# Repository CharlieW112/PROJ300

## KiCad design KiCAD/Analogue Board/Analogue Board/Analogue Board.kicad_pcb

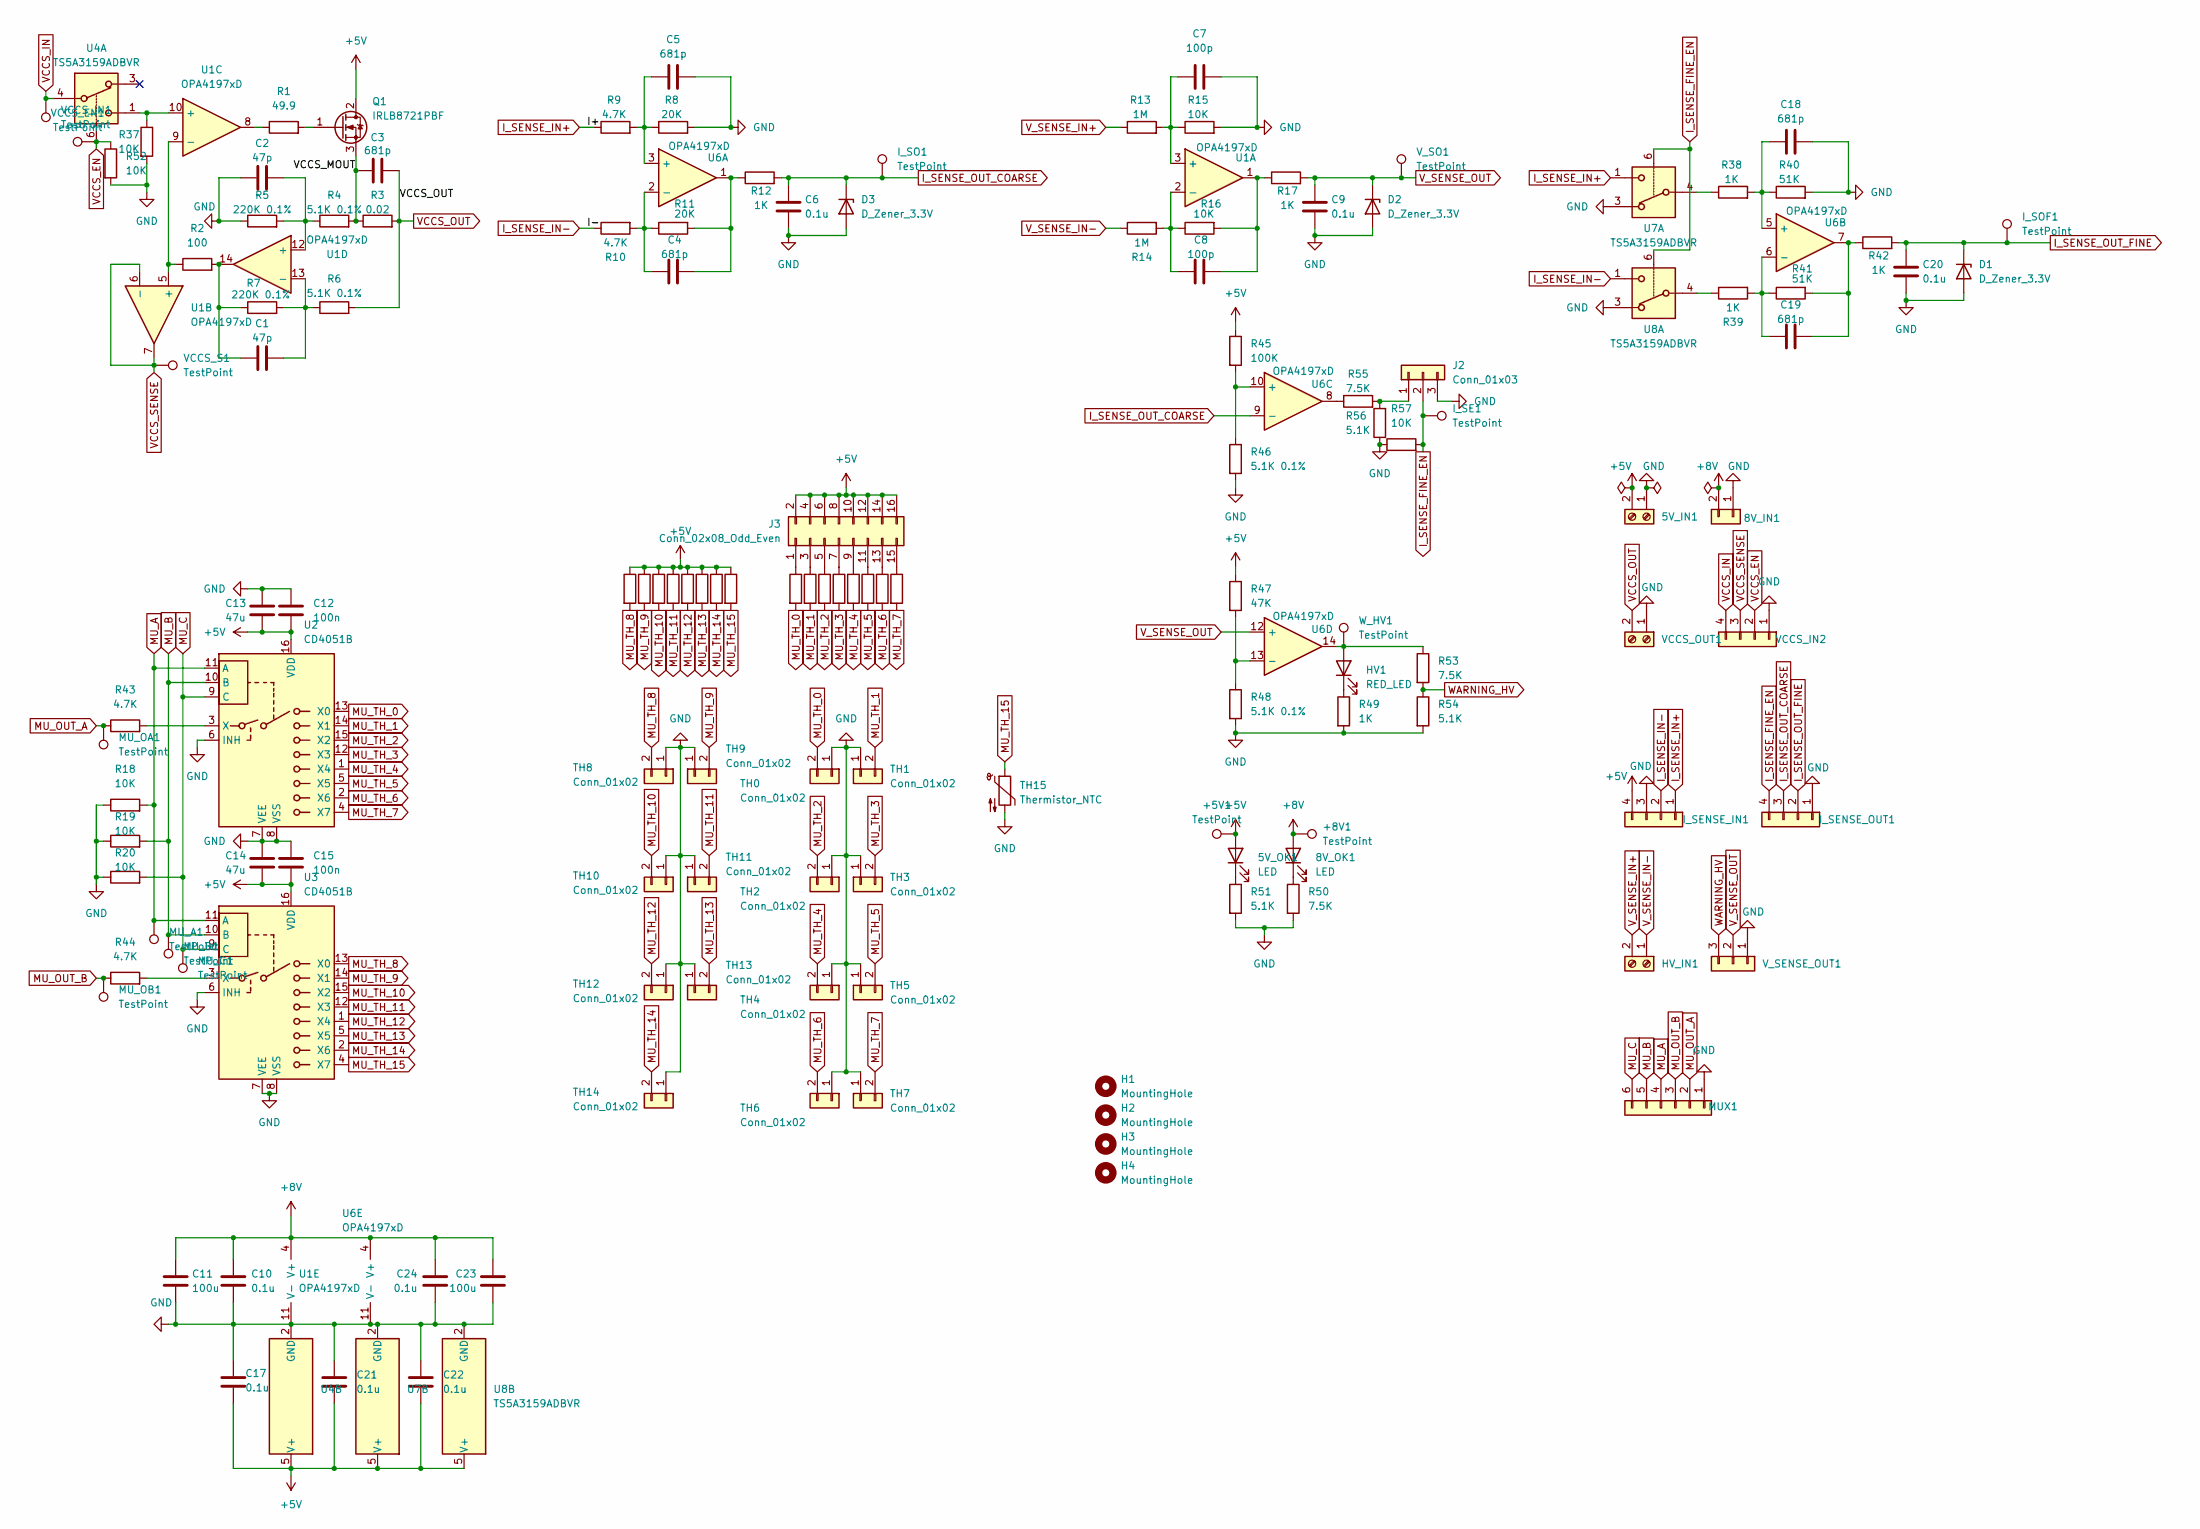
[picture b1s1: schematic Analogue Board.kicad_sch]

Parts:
5V_IN1: Screw_Terminal_01x02; TerminalBlock_bornier-2_P5.08mm
5V_OK1, 8V_OK1: LED; D_0603_1608Metric_Pad1.05x0.95mm_HandSolder
8V_IN1: Conn_01x02; JST_XH_B2B-XH-A_1x02_P2.50mm_Vertical
+5V1, +8V1: TestPoint; TestPoint_Pad_1.5x1.5mm
C1, C2: 47p; C_0201_0603Metric_Pad0.64x0.40mm_HandSolder
C3, C4, C5, C18, C19: 681p; C_0201_0603Metric_Pad0.64x0.40mm_HandSolder
C6, C9, C10, C17, C20, C21, C22, C24: 0.1u; C_0603_1608Metric_Pad1.08x0.95mm_HandSolder
C7, C8: 100p; C_0402_1005Metric_Pad0.74x0.62mm_HandSolder
C11, C23: 100u; C_Radial_D6.3mm_H11.0mm_P2.50mm
C12, C15: 100n; C_0603_1608Metric_Pad1.08x0.95mm_HandSolder
C13, C14: 47u; C_Radial_D6.3mm_H11.0mm_P2.50mm
D1, D2, D3: D_Zener_3.3V; D_SOD-123
H1, H2, H3, H4: MountingHole; MountingHole_3.2mm_M3
HV1: RED_LED; D_0603_1608Metric_Pad1.05x0.95mm_HandSolder
HV_IN1: Screw_Terminal_01x02; TerminalBlock_bornier-2_P5.08mm
I_SE1: TestPoint; TestPoint_Pad_1.5x1.5mm
I_SENSE_IN1: Conn_01x04; JST_XH_B4B-XH-A_1x04_P2.50mm_Vertical
I_SENSE_OUT1: Conn_01x04; JST_XH_B4B-XH-A_1x04_P2.50mm_Vertical
I_SO1: TestPoint; TestPoint_Pad_1.5x1.5mm
I_SOF1: TestPoint; TestPoint_Pad_1.5x1.5mm
J2: Conn_01x03; PinHeader_1x03_P2.54mm_Vertical
J3: Conn_02x08_Odd_Even; PinHeader_2x08_P2.54mm_Vertical
MUX1: Conn_01x06; JST_XH_B6B-XH-A_1x06_P2.50mm_Vertical
MU_A1: TestPoint; TestPoint_Pad_1.5x1.5mm
MU_B1: TestPoint; TestPoint_Pad_1.5x1.5mm
MU_C1: TestPoint; TestPoint_Pad_1.5x1.5mm
MU_OA1: TestPoint; TestPoint_Pad_1.5x1.5mm
MU_OB1: TestPoint; TestPoint_Pad_1.5x1.5mm
Q1: IRLB8721PBF; TO-220-3_Vertical
R1: 49.9; R_0402_1005Metric_Pad0.72x0.64mm_HandSolder
R2: 100; R_0603_1608Metric_Pad0.98x0.95mm_HandSolder
R3: 0.02; R_2010_5025Metric_Pad1.40x2.65mm_HandSolder
R4, R6, R46, R48: 5.1K 0.1%; R_0603_1608Metric_Pad0.98x0.95mm_HandSolder
R5, R7: 220K 0.1%; R_0805_2012Metric_Pad1.20x1.40mm_HandSolder
R8, R11: 20K; R_0402_1005Metric_Pad0.72x0.64mm_HandSolder
R9, R10, R43, R44: 4.7K; R_0603_1608Metric_Pad0.98x0.95mm_HandSolder
R12, R17, R38, R39, R42, R49: 1K; R_0603_1608Metric_Pad0.98x0.95mm_HandSolder
R13, R14: 1M; R_Axial_DIN0207_L6.3mm_D2.5mm_P7.62mm_Horizontal
R15, R16, R18, R19, R20, R37, R52, R57: 10K; R_0603_1608Metric_Pad0.98x0.95mm_HandSolder
R21, R22, R23, R24, R25, R26, R27, R28, R29, R30, R31, R32, R33, R34, R35, R36: 10K 0.5%; R_0805_2012Metric_Pad1.20x1.40mm_HandSolder
R40, R41: 51K; R_0603_1608Metric_Pad0.98x0.95mm_HandSolder
R45: 100K; R_0402_1005Metric_Pad0.72x0.64mm_HandSolder
R47: 47K; R_0603_1608Metric_Pad0.98x0.95mm_HandSolder
R50, R53, R55: 7.5K; R_0603_1608Metric_Pad0.98x0.95mm_HandSolder
R51, R54, R56: 5.1K; R_0603_1608Metric_Pad0.98x0.95mm_HandSolder
TH0, TH1, TH2, TH3, TH4, TH5, TH6, TH7, TH8, TH9, TH10, TH11, TH12, TH13, TH14: Conn_01x02; JST_XH_B2B-XH-A_1x02_P2.50mm_Vertical
TH15: Thermistor_NTC; R_0805_2012Metric_Pad1.20x1.40mm_HandSolder
U1, U6: OPA4197xD; SOIC-14_3.9x8.7mm_P1.27mm
U2, U3: CD4051B; DIP-16_W7.62mm
U4, U7, U8: TS5A3159ADBVR; SOT-23-6
VCCS_EN1: TestPoint; TestPoint_Pad_1.5x1.5mm
VCCS_IN1: TestPoint; TestPoint_Pad_1.5x1.5mm
VCCS_IN2: Conn_01x04; JST_XH_B4B-XH-A_1x04_P2.50mm_Vertical
VCCS_OUT1: Screw_Terminal_01x02; TerminalBlock_bornier-2_P5.08mm
VCCS_S1: TestPoint; TestPoint_Pad_1.5x1.5mm
V_SENSE_OUT1: Conn_01x03; JST_XH_B3B-XH-A_1x03_P2.50mm_Vertical
V_SO1: TestPoint; TestPoint_Pad_1.5x1.5mm
W_HV1: TestPoint; TestPoint_Pad_1.5x1.5mm

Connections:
+5V: 5V_IN1.2, 5V_OK1.2 (A), +5V1.1, C12.2, C13.2, C14.2, C15.2, C17.2, C21.2, C22.2, I_SENSE_IN1.4, J3.2, J3.4, J3.6, J3.8, J3.10, J3.12, J3.14, J3.16, Q1.2 (D), R29.1, R30.1, R31.1, R32.1, R33.1, R34.1, R35.1, R36.1, R45.1, R47.1, U2.16 (VDD), U3.16 (VDD), U4.5 (V+), U7.5 (V+), U8.5 (V+)
+8V: 8V_IN1.2, 8V_OK1.2 (A), +8V1.1, C10.1, C11.1, C23.1, C24.1, U1.4 (V+), U6.4 (V+)
/VCCS_MOUT: C3.1, Q1.3 (S), R3.1, R4.2
GND: 5V_IN1.1, 8V_IN1.1, C2.1, C5.2, C6.2, C7.2, C9.2, C10.2, C11.2, C12.1, C13.1, C14.1, C15.1, C17.1, C18.2, C20.2, C21.1, C22.1, C23.2, C24.2, D1.2 (A), D2.2 (A), D3.2 (A), I_SENSE_IN1.3, I_SENSE_OUT1.1, J2.3, MUX1.1, R5.1, R8.2, R15.2, R18.1, R19.1, R20.1, R37.2, R40.2, R46.2, R48.2, R49.2, R50.2, R51.2, R52.2, R54.2, R56.1, R57.1, TH0.1, TH1.1, TH2.1, TH3.1, TH4.1, TH5.1, TH6.1, TH7.1, TH8.1, TH9.1, TH10.1, TH11.1, TH12.1, TH13.1, TH14.1, TH15.2, U1.11 (V-), U2.6 (INH), U2.7 (VEE), U2.8 (VSS), U3.6 (INH), U3.7 (VEE), U3.8 (VSS), U4.2 (GND), U6.11 (V-), U7.2 (GND), U7.3, U8.2 (GND), U8.3, VCCS_IN2.1, VCCS_OUT1.1, V_SENSE_OUT1.1
I_SENSE_FINE_EN: I_SE1.1, I_SENSE_OUT1.4, J2.2, R57.2, U7.6, U8.6
I_SENSE_IN+: I_SENSE_IN1.1, R9.1, U7.1
I_SENSE_IN-: I_SENSE_IN1.2, R10.1, U8.1
I_SENSE_OUT_COARSE: C6.1, D3.1 (K), I_SENSE_OUT1.3, I_SO1.1, R12.2, U6.9 (-)
I_SENSE_OUT_FINE: C20.1, D1.1 (K), I_SENSE_OUT1.2, I_SOF1.1, R42.2
MU_A: MUX1.4, MU_A1.1, R18.2, U2.11 (A), U3.11 (A)
MU_B: MUX1.5, MU_B1.1, R19.2, U2.10 (B), U3.10 (B)
MU_C: MUX1.6, MU_C1.1, R20.2, U2.9 (C), U3.9 (C)
MU_OUT_A: MUX1.2, MU_OA1.1, R43.1
MU_OUT_B: MUX1.3, MU_OB1.1, R44.1
MU_TH_0: R21.2, TH0.2, U2.13 (X0)
MU_TH_1: R22.2, TH1.2, U2.14 (X1)
MU_TH_2: R23.2, TH2.2, U2.15 (X2)
MU_TH_3: R24.2, TH3.2, U2.12 (X3)
MU_TH_4: R25.2, TH4.2, U2.1 (X4)
MU_TH_5: R26.2, TH5.2, U2.5 (X5)
MU_TH_6: R27.2, TH6.2, U2.2 (X6)
MU_TH_7: R28.2, TH7.2, U2.4 (X7)
MU_TH_8: R29.2, TH8.2, U3.13 (X0)
MU_TH_9: R30.2, TH9.2, U3.14 (X1)
MU_TH_10: R31.2, TH10.2, U3.15 (X2)
MU_TH_11: R32.2, TH11.2, U3.12 (X3)
MU_TH_12: R33.2, TH12.2, U3.1 (X4)
MU_TH_13: R34.2, TH13.2, U3.5 (X5)
MU_TH_14: R35.2, TH14.2, U3.2 (X6)
MU_TH_15: R36.2, TH15.1, U3.4 (X7)
unnamed: 5V_OK1.1 (K), R51.1
unnamed: 8V_OK1.1 (K), R50.1
unnamed: C1.1, R2.2, R7.1, U1.14
unnamed: C4.2, R11.2, R12.1, U6.1
unnamed: C8.2, R16.2, R17.1, U1.1
unnamed: C19.2, R41.2, R42.1, U6.7
unnamed: HV1.2 (A), R53.1, U6.14, W_HV1.1
unnamed: HV1.1 (K), R49.1
unnamed: J2.1, R55.2, R56.2
unnamed: J3.1, R21.1
unnamed: J3.3, R22.1
unnamed: J3.5, R23.1
unnamed: J3.7, R24.1
unnamed: J3.9, R25.1
unnamed: J3.11, R26.1
unnamed: J3.13, R27.1
unnamed: J3.15, R28.1
unnamed: Q1.1 (G), R1.2
unnamed: R1.1, U1.8
unnamed: R38.1, U7.4
unnamed: R39.1, U8.4
unnamed: R55.1, U6.8
unnamed: C7.1, R13.2, R15.1, U1.3 (+)
unnamed: C8.1, R14.2, R16.1, U1.2 (-)
unnamed: R2.1, U1.5 (+), U1.9 (-)
unnamed: R37.1, U1.10 (+), U4.1
unnamed: C2.2, R4.1, R5.2, U1.12 (+)
unnamed: C1.2, R6.1, R7.2, U1.13 (-)
unnamed: R43.2, U2.3 (X)
unnamed: R44.2, U3.3 (X)
unnamed: C5.1, R8.1, R9.2, U6.3 (+)
unnamed: C4.1, R10.2, R11.1, U6.2 (-)
unnamed: C18.1, R38.2, R40.1, U6.5 (+)
unnamed: C19.1, R39.2, R41.1, U6.6 (-)
unnamed: R45.2, R46.1, U6.10 (+)
unnamed: R47.2, R48.1, U6.13 (-)
VCCS_EN: R52.1, U4.6, VCCS_EN1.1, VCCS_IN2.2
VCCS_IN: U4.4, VCCS_IN1.1, VCCS_IN2.4
VCCS_OUT: C3.2, R3.2, R6.2, VCCS_OUT1.2
VCCS_SENSE: U1.6 (-), U1.7, VCCS_IN2.3, VCCS_S1.1
V_SENSE_IN+: HV_IN1.2, R13.1
V_SENSE_IN-: HV_IN1.1, R14.1
V_SENSE_OUT: C9.1, D2.1 (K), R17.2, U6.12 (+), V_SENSE_OUT1.2, V_SO1.1
WARNING_HV: R53.2, R54.1, V_SENSE_OUT1.3

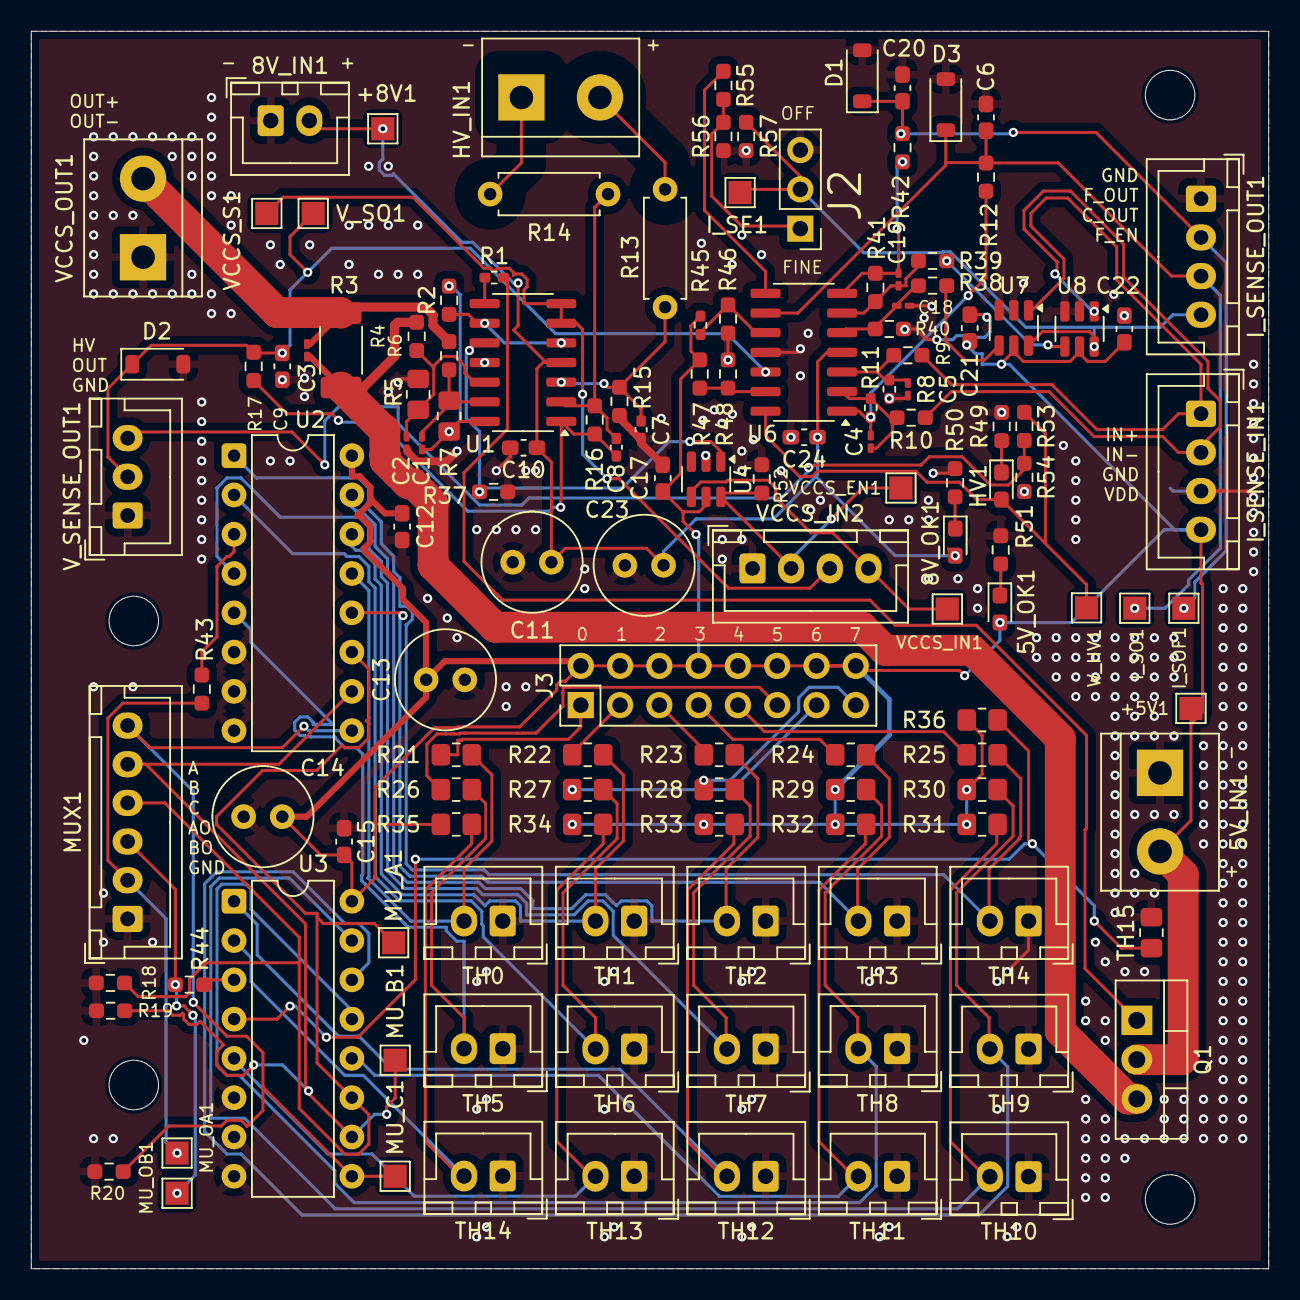
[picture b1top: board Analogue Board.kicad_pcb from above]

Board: 2 copper layers, 80.0 x 80.0 mm, 140 parts (0 on the bottom side), 74 nets.

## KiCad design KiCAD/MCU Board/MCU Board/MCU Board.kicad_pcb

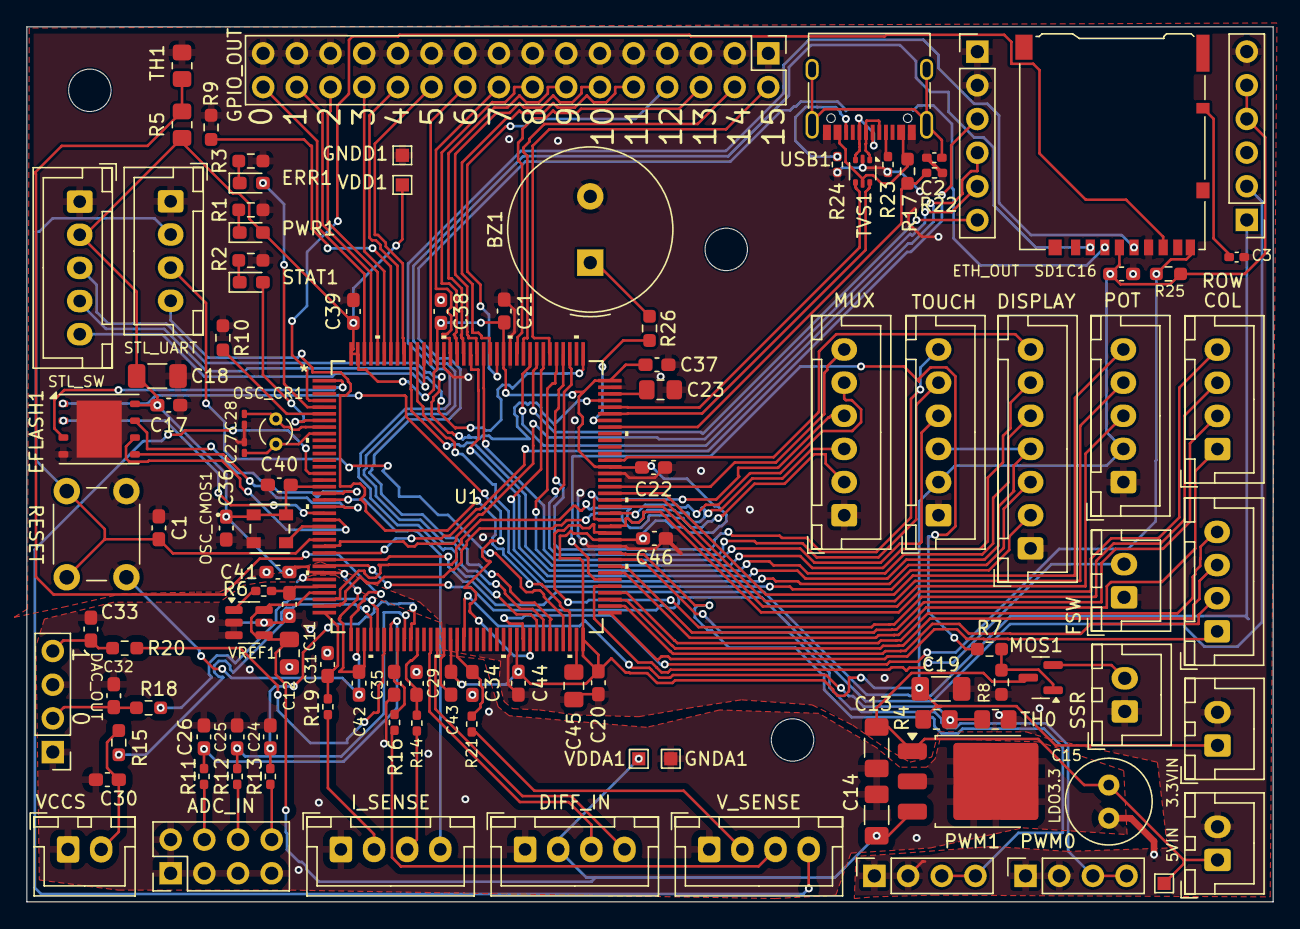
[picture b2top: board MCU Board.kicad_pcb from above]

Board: 2 copper layers, 94.0 x 66.0 mm, 114 parts (0 on the bottom side), 127 nets.

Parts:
3.3VIN, 5VIN: Conn_01x02; JST_XH_B2B-XH-A_1x02_P2.50mm_Vertical
5VIN2: TestPoint; TestPoint_Pad_1.0x1.0mm
ADC_IN: Conn_02x04_Odd_Even; PinHeader_2x04_P2.54mm_Vertical
BZ1: Buzzer; Buzzer_TDK_PS1240P02BT_D12.2mm_H6.5mm
C1: 100n; C_0603_1608Metric_Pad1.08x0.95mm_HandSolder
C2, C3: 10n; C_0402_1005Metric_Pad0.74x0.62mm_HandSolder
C11, C16, C17, C21, C22, C24, C25, C26, C29, C30, C31, C32, C33, C34, C35, C36, C37, C38, C39, C40, C41, C42, C43, C44, C45, C46: 0.1u; C_0603_1608Metric_Pad1.08x0.95mm_HandSolder
C12, C20, C23: 1u; C_0805_2012Metric_Pad1.18x1.45mm_HandSolder
C13, C14, C18, C19: 10u; C_1206_3216Metric_Pad1.33x1.80mm_HandSolder
C15: 100u; C_Radial_D6.3mm_H11.0mm_P2.50mm
C27, C28: 10p; C_0201_0603Metric_Pad0.64x0.40mm_HandSolder
COL: Conn_01x04; JST_XH_B4B-XH-A_1x04_P2.50mm_Vertical
DAC_OUT: Conn_01x04; PinHeader_1x04_P2.54mm_Vertical
DIFF_IN: Conn_01x04; JST_XH_B4B-XH-A_1x04_P2.50mm_Vertical
DISPLAY: Conn_01x07; JST_XH_B7B-XH-A_1x07_P2.50mm_Vertical
EFLASH1: W25Q128JVP; WSON-8-1EP_6x5mm_P1.27mm_EP3.4x4.3mm
ERR1: Red LED; D_0603_1608Metric_Pad1.05x0.95mm_HandSolder
ETH_OUT, ETH_OUT1: Conn_01x06; PinHeader_1x06_P2.54mm_Vertical
FSW: Conn_01x02; JST_XH_B2B-XH-A_1x02_P2.50mm_Vertical
GNDA1: TestPoint; TestPoint_Pad_1.0x1.0mm
GNDD1: TestPoint; TestPoint_Pad_1.0x1.0mm
GPIO_OUT: Conn_02x16_Odd_Even; PinHeader_2x16_P2.54mm_Vertical
H1, H2, H3: MountingHole; MountingHole_3.2mm_M3
I_SENSE: Conn_01x04; JST_XH_B4B-XH-A_1x04_P2.50mm_Vertical
LDO3.3: TO-252-3_TabPin2
MOS1: AO3400A; SOT-23
MUX: Conn_01x06; JST_XH_B6B-XH-A_1x06_P2.50mm_Vertical
NT1: NetTie_2; NetTie-2_SMD_Pad0.5mm
OSC_CMOS1: COM1305-25.000; SMD4_COM1305_2p5x3p2x1p0_RAL-M
OSC_CR1: AB26T-32.768KHZ; Crystal_C26-LF_D2.1mm_L6.5mm_Vertical
POT: Conn_01x05; JST_XH_B5B-XH-A_1x05_P2.50mm_Vertical
PWM0, PWM1: Conn_01x04; PinSocket_1x04_P2.54mm_Vertical
PWR1: Green LED; D_0603_1608Metric_Pad1.05x0.95mm_HandSolder
R1, R2, R3, R7: 1K; R_0603_1608Metric_Pad0.98x0.95mm_HandSolder
R4, R5: 10K 0.5%; R_0805_2012Metric_Pad1.20x1.40mm_HandSolder
R6: 10; R_0402_1005Metric_Pad0.72x0.64mm_HandSolder
R8, R10, R17, R25: 10K; R_0603_1608Metric_Pad0.98x0.95mm_HandSolder
R9: 10k; R_0603_1608Metric_Pad0.98x0.95mm_HandSolder
R11, R12, R13, R14, R16, R19, R21: 49.9; R_0402_1005Metric_Pad0.72x0.64mm_HandSolder
R15, R18, R20, R26: 100; R_0603_1608Metric_Pad0.98x0.95mm_HandSolder
R22: 20K; R_0402_1005Metric_Pad0.72x0.64mm_HandSolder
R23, R24: 5.1K; R_0402_1005Metric_Pad0.72x0.64mm_HandSolder
RESET: SW_Push; SW_PUSH_6mm_H9.5mm
ROW: Conn_01x04; JST_XH_B4B-XH-A_1x04_P2.50mm_Vertical
SD1: Micro_SD_Card_Det1; microSD_HC_Hirose_DM3AT-SF-PEJM5
SSR: Conn_01x02; JST_XH_B2B-XH-A_1x02_P2.50mm_Vertical
STAT1: Green LED; D_0603_1608Metric_Pad1.05x0.95mm_HandSolder
STL_SW: Conn_01x05; JST_XH_B5B-XH-A_1x05_P2.50mm_Vertical
STL_UART: Conn_01x04; JST_XH_B4B-XH-A_1x04_P2.50mm_Vertical
TH0, TH1: Thermistor_NTC; R_0805_2012Metric_Pad1.20x1.40mm_HandSolder
TOUCH: Conn_01x06; JST_XH_B6B-XH-A_1x06_P2.50mm_Vertical
TVS1: USBLC6-2P6; SOT-666
U1: STM32H7A3ZIT6; LQFP-144-M
USB1: USB_C_Receptacle_USB2.0_16P; USB_C_Receptacle_XKB_U262-16XN-4BVC11
VCCS: Conn_01x02; JST_XH_B2B-XH-A_1x02_P2.50mm_Vertical
VDD1: TestPoint; TestPoint_Pad_1.0x1.0mm
VDDA1: TestPoint; TestPoint_Pad_1.0x1.0mm
VREF1: MCP1501-33xCH; SOT-23-6
V_SENSE: Conn_01x04; JST_XH_B4B-XH-A_1x04_P2.50mm_Vertical

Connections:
3.3VREF: C11.1, R6.2, U1.32 (VREF+)
+5V: 5VIN.1, 5VIN2.1, C13.1, C15.1, LDO3.3.1 (IN), MOS1.3 (D)
/USB+: TVS1.3 (I/O2), USB1.A6 (D+), USB1.B6 (D+)
/USB-: TVS1.1 (I/O1), USB1.A7 (D-), USB1.B7 (D-)
ADC0_UNUSED: C26.1, R11.2, U1.43 (ADC0_UNUSED)
ADC1_UNUSED: C25.1, R12.2, U1.45 (ADC1_UNUSED)
ADC2_UNUSED: C24.1, R13.2, U1.46 (ADC2_UNUSED)
ADC_DIFF_N: DIFF_IN.4, U1.50 (ADC_DIFF_N)
ADC_DIFF_P: DIFF_IN.3, U1.49 (ADC_DIFF_P)
ADC_ISENSEC: C29.2, R14.1, U1.47 (ADC_ISENSEC)
ADC_ISENSEF: C31.1, R19.1, U1.36 (ADC_ISENSEF)
ADC_VCCSSENSE: C35.2, R16.1, U1.44 (ADC_VCCSSENSE)
ADC_VSENSE: C34.1, R21.1, U1.53 (ADC_VSENSE)
DAC0_UNUSED: R18.1, U1.41 (DAC0_UNUSED)
DAC1_UNUSED: R20.1, U1.42 (DAC1_UNUSED)
DAC_VCCS: R15.1, U1.40 (DAC_VCCS)
DISPL_CS: DISPLAY.2, U1.134 (DISPL_CS)
DISPL_DC: DISPLAY.6, U1.113 (DISPL_DC)
DISPL_LED: DISPLAY.7, U1.96 (DISPL_LED)
DISPL_MOSI: DISPLAY.5, U1.135 (DISPL_MOSI)
DISPL_RST: DISPLAY.3, U1.115 (DISPL_RST)
DISPL_SCK: DISPLAY.4, TOUCH.3, U1.126 (DISPL_SCK)
DTH2: R4.2, TH0.1, U1.54 (DTH2)
DTH3: R5.2, TH1.1, U1.37 (DTH3)
ENCODER_A: POT.3, U1.89 (ENCODER_A)
ENCODER_B: POT.4, U1.90 (ENCODER_B)
ENCODER_SW: POT.5, U1.91 (ENCODER_SW)
ERROR_LED: ERR1.2 (A), U1.5 (ERROR_LED)
ETH_CS: ETH_OUT.5, U1.26 (ETH_CS)
ETH_INT: ETH_OUT.6, U1.116 (ETH_INT)
ETH_MISO: ETH_OUT1.1, U1.28 (ETH_MISO)
ETH_MOSI: ETH_OUT.3, U1.27 (ETH_MOSI)
ETH_RST: ETH_OUT1.2, U1.29 (ETH_RST)
ETH_SCK: ETH_OUT.4, U1.117 (ETH_SCK)
E_FLASH_CLK: EFLASH1.6 (CLK), U1.22 (E_FLASH_CLK)
E_FLASH_CS: EFLASH1.1 (~CS), U1.64 (E_FLASH_CS)
E_FLASH_IO0: EFLASH1.5 (DI/IO_{0}), U1.20 (E_FLASH_IO0)
E_FLASH_IO1: EFLASH1.2 (DO/IO_{1}), U1.21 (E_FLASH_IO1)
E_FLASH_IO2: EFLASH1.3 (~WP/IO_{2}), U1.1 (E_FLASH_IO2)
E_FLASH_IO3: EFLASH1.7 (~HOLD/~RESET/IO_{3}), U1.18 (E_FLASH_IO3)
FRONT_SW: FSW.2, U1.77 (FRONT_SW)
GNDA: ADC_IN.1, ADC_IN.2, ADC_IN.3, ADC_IN.5, ADC_IN.7, C11.2, C12.2, C13.2, C14.2, C15.2, C24.2, C25.2, C26.2, C29.1, C30.1, C31.2, C32.1, C33.2, C34.2, C35.1, DAC_OUT.1, DAC_OUT.3, DIFF_IN.1, GNDA1.1, I_SENSE.1, LDO3.3.2 (GND), NT1.2, U1.31 (VSSA), VCCS.1, VREF1.2 (GND), VREF1.3 (GND), VREF1.5 (GND), V_SENSE.1
GNDD: 3.3VIN.2, 5VIN.2, BZ1.2 (-), C1.2, C2.2, C3.2, C16.1, C17.2, C18.2, C19.2, C20.2, C21.2, C22.2, C23.2, C27.2, C28.2, C36.2, C37.1, C38.1, C39.1, C40.1, C41.1, C42.1, C43.1, C44.1, C45.1, C46.1, DISPLAY.1, EFLASH1.4 (GND), EFLASH1.9 (EP), ETH_OUT.1, ETH_OUT.2, ETH_OUT1.6, FSW.1, GNDD1.1, GPIO_OUT.1, GPIO_OUT.3, GPIO_OUT.5, GPIO_OUT.7, GPIO_OUT.9, GPIO_OUT.11, GPIO_OUT.13, GPIO_OUT.15, GPIO_OUT.17, GPIO_OUT.19, GPIO_OUT.21, GPIO_OUT.23, GPIO_OUT.25, GPIO_OUT.27, GPIO_OUT.29, GPIO_OUT.31, MUX.1, NT1.1, OSC_CMOS1.2 (GND), POT.1, PWM0.1, PWM0.2, PWM1.1, PWM1.2, R1.2, R2.2, R3.2, R8.2, R9.2, R10.1, R22.2, R23.2, R24.2, RESET.2, SD1.6 (VSS), SSR.1, STL_SW.1, STL_UART.1, TH0.2, TH1.2, TOUCH.1, TVS1.2 (GND), U1.16 (VSS), U1.38 (VSS), U1.51 (VSS), U1.61 (VSS), U1.83 (VSS), U1.94 (VSS), U1.107 (VSS), U1.120 (VSS), U1.130 (VSS), USB1.A1 (GND), USB1.A12 (GND), USB1.B1 (GND), USB1.B12 (GND)
GPIO0_UNUSED: GPIO_OUT.32, U1.142 (GPIO0_UNUSED)
GPIO1_UNUSED: GPIO_OUT.30, U1.141 (GPIO1_UNUSED)
GPIO2_UNUSED: GPIO_OUT.28, U1.140 (GPIO2_UNUSED)
GPIO3_UNUSED: GPIO_OUT.26, U1.139 (GPIO3_UNUSED)
GPIO4_UNUSED: GPIO_OUT.24, U1.137 (GPIO4_UNUSED)
GPIO5_UNUSED: GPIO_OUT.22, U1.136 (GPIO5_UNUSED)
GPIO6_UNUSED: GPIO_OUT.20, U1.132 (GPIO6_UNUSED)
GPIO7_UNUSED: GPIO_OUT.18, U1.129 (GPIO7_UNUSED)
GPIO8_UNUSED: GPIO_OUT.16, U1.128 (GPIO8_UNUSED)
GPIO9_UNUSED: GPIO_OUT.14, U1.127 (GPIO9_UNUSED)
GPIO10_UNUSED: GPIO_OUT.12, U1.125 (GPIO10_UNUSED)
GPIO11_UNUSED: GPIO_OUT.10, U1.123 (GPIO11_UNUSED)
GPIO12_UNUSED: GPIO_OUT.8, U1.122 (GPIO12_UNUSED)
GPIO13_UNUSED: GPIO_OUT.6, U1.119 (GPIO13_UNUSED)
GPIO14_UNUSED: GPIO_OUT.4, U1.118 (GPIO14_UNUSED)
GPIO15_UNUSED: GPIO_OUT.2, U1.114 (GPIO15_UNUSED)
GPIO_I_SENSE_EN: I_SENSE.4, U1.19 (PF7)
GPIO_WARNING_HV: U1.15 (PF5), V_SENSE.4
HSE_OSC: OSC_CMOS1.3 (OUT), U1.23 (HSE_OSC)
MATC0: COL.1, U1.73 (MATC0)
MATC1: COL.2, U1.74 (MATC1)
MATC2: COL.3, U1.75 (MATC2)
MATC3: COL.4, U1.76 (MATC3)
MATR0: ROW.1, U1.79 (MATR0)
MATR1: ROW.2, U1.80 (MATR1)
MATR2: ROW.3, U1.85 (MATR2)
MATR3: ROW.4, U1.86 (MATR3)
MUX_A: MUX.4, U1.87 (PG2)
MUX_B: MUX.5, U1.88 (PG3)
MUX_C: MUX.6, U1.92 (PG7)
MUX_TH0: MUX.2, U1.35 (MUX_TH0)
MUX_TH1: MUX.3, U1.34 (MUX_TH1)
NRST: C1.1, RESET.1, STL_UART.2, U1.25 (NRST)
unnamed: ADC_IN.4, R11.1
unnamed: ADC_IN.6, R12.1
unnamed: ADC_IN.8, R13.1
unnamed: BZ1.1 (+), R26.2
unnamed: C32.2, DAC_OUT.2, R18.2
unnamed: C33.1, DAC_OUT.4, R20.2
unnamed: ERR1.1 (K), R3.1
unnamed: I_SENSE.2, R19.2
unnamed: I_SENSE.3, R14.2
unnamed: MOS1.1 (G), R7.2, R8.1
unnamed: PWR1.1 (K), R1.1
unnamed: C3.1, SD1.10 (SHIELD)
unnamed: R2.1, STAT1.1 (K)
unnamed: R17.1, TVS1.5 (VBUS), USB1.A4 (VBUS), USB1.A9 (VBUS), USB1.B4 (VBUS), USB1.B9 (VBUS)
unnamed: R10.2, U1.6 (VBAT)
unnamed: C20.1, U1.71 (VCAP)
unnamed: R9.1, U1.138 (BOOT0)
unnamed: C23.1, U1.106 (VCAP)
unnamed: R23.1, USB1.A5 (CC1)
unnamed: R24.1, USB1.B5 (CC2)
unnamed: C2.1, USB1.S1 (SHIELD)
unnamed: C30.2, R15.2, VCCS.2
unnamed: R6.1, VREF1.1 (OUT)
unnamed: R21.2, V_SENSE.2
unnamed: R16.2, V_SENSE.3
PWM0: PWM0.3, PWM0.4, U1.81 (PWM0)
PWM1: PWM1.3, PWM1.4, U1.82 (PWM1)
PWM_BUZZER: R26.1, U1.102 (PA10)
RTC_OSC_IN: C28.1, OSC_CR1.1, U1.8 (RTC_OSC_IN)
RTC_OSC_OUT: C27.1, OSC_CR1.2, U1.9 (RTC_OSC_OUT)
SD_CARD_DETECT: R25.1, SD1.9 (DET), U1.63 (SD_CARD_DETECT)
SD_CS: SD1.2 (DAT3/CD), U1.66 (SD_CS)
SD_MISO: SD1.7 (DAT0), U1.4 (SD_MISO)
SD_MOSI: SD1.3 (CMD), U1.67 (SD_MOSI)
SD_SCK: SD1.5 (CLK), U1.65 (SD_SCK)
SSR_EN: R7.1, U1.78 (SSR_EN)
SSR_OUT: MOS1.2 (S), SSR.2
STATUS_LED: STAT1.2 (A), U1.7 (STATUS_LED)
ST_LINK_RX: STL_UART.4, U1.70 (ST_LINK_RX)
ST_LINK_SWCLK: STL_SW.4, U1.109 (ST_LINK_SWCLK)
ST_LINK_SWDIO: STL_SW.3, U1.105 (ST_LINK_SWDIO)
ST_LINK_SWO: STL_SW.5, U1.133 (ST_LINK_SWO)
ST_LINK_TX: STL_UART.3, U1.69 (ST_LINK_TX)
TOUCH_CS: TOUCH.5, U1.111 (TOUCH_CS)
TOUCH_INT: TOUCH.6, U1.112 (TOUCH_INT)
TOUCH_MISO: TOUCH.4, U1.124 (TOUCH_MISO)
USB_DM: TVS1.6 (I/O1), U1.103 (USB_DM)
USB_DP: TVS1.4 (I/O2), U1.104 (USB_DP)
USB_VBUS: R17.2, R22.1, U1.101 (USB_VBUS)
VDD: 3.3VIN.1, C16.2, C17.1, C18.1, C19.1, C21.1, C22.1, C36.1, C37.2, C38.2, C39.2, C40.2, C41.2, C42.2, C43.2, C44.2, C45.2, C46.2, EFLASH1.8 (VCC), ETH_OUT1.4, ETH_OUT1.5, OSC_CMOS1.1 (EN), OSC_CMOS1.4 (Vdd), POT.2, PWR1.2 (A), R4.1, R5.1, R25.2, SD1.4 (VDD), STL_SW.2, TOUCH.2, U1.17 (VDD), U1.30 (VDD), U1.39 (VDD), U1.52 (VDD), U1.62 (VDD), U1.72 (VDD), U1.84 (VDD), U1.95 (VDD33USB), U1.108 (VDD), U1.121 (VDDMMC), U1.131 (VDD), U1.143 (PDR_ON), U1.144 (VDD), VDD1.1
VDDA: C12.1, C14.1, DIFF_IN.2, LDO3.3.3 (OUT), U1.33 (VDDA), VDDA1.1, VREF1.4 (~SHDN), VREF1.6 (VDD)

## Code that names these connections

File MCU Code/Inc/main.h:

/* USER CODE BEGIN Header */
/**
  ******************************************************************************
  * @file           : main.h
  * @brief          : Header for main.c file.
  *                   This file contains the common defines of the application.
  ******************************************************************************
  * @attention
  *
  * Copyright (c) 2025 STMicroelectronics.
  * All rights reserved.
  *
  * This software is licensed under terms that can be found in the LICENSE file
  * in the root directory of this software component.
  * If no LICENSE file comes with this software, it is provided AS-IS.
  *
  ******************************************************************************
  */
/* USER CODE END Header */

/* Define to prevent recursive inclusion -------------------------------------*/
#ifndef __MAIN_H
#define __MAIN_H

#ifdef __cplusplus
extern "C" {
#endif

/* Includes ------------------------------------------------------------------*/
#include "stm32h7xx_hal.h"

/* Private includes ----------------------------------------------------------*/
/* USER CODE BEGIN Includes */
#include "z_displ_ILI9XXX.h"
#include "z_touch_XPT2046.h"
#include "fonts.h"
#include "thermistor_mux.h"


/* USER CODE END Includes */

/* Exported types ------------------------------------------------------------*/
/* USER CODE BEGIN ET */

/* USER CODE END ET */

/* Exported constants --------------------------------------------------------*/
/* USER CODE BEGIN EC */

/* USER CODE END EC */

/* Exported macro ------------------------------------------------------------*/
/* USER CODE BEGIN EM */

/* USER CODE END EM */

void HAL_TIM_MspPostInit(TIM_HandleTypeDef *htim);

/* Exported functions prototypes ---------------------------------------------*/
void Error_Handler(void);

/* USER CODE BEGIN EFP */

/* USER CODE END EFP */

/* Private defines -----------------------------------------------------------*/
#define ERROR_LED_Pin GPIO_PIN_6
#define ERROR_LED_GPIO_Port GPIOE
#define STATUS_LED_Pin GPIO_PIN_13
#define STATUS_LED_GPIO_Port GPIOC
#define RTC_OSC_IN_Pin GPIO_PIN_14
#define RTC_OSC_IN_GPIO_Port GPIOC
#define RTC_OSC_OUT_Pin GPIO_PIN_15
#define RTC_OSC_OUT_GPIO_Port GPIOC
#define GPIO_WARNING_HV_Pin GPIO_PIN_5
#define GPIO_WARNING_HV_GPIO_Port GPIOF
#define GPIO_I_SENSE_ENABLE_Pin GPIO_PIN_7
#define GPIO_I_SENSE_ENABLE_GPIO_Port GPIOF
#define HSE_OSC_Pin GPIO_PIN_0
#define HSE_OSC_GPIO_Port GPIOH
#define ETH_CS_Pin GPIO_PIN_0
#define ETH_CS_GPIO_Port GPIOC
#define ETH_RST_Pin GPIO_PIN_3
#define ETH_RST_GPIO_Port GPIOC
#define MUX_TH1_Pin GPIO_PIN_0
#define MUX_TH1_GPIO_Port GPIOA
#define MUX_TH0_Pin GPIO_PIN_1
#define MUX_TH0_GPIO_Port GPIOA
#define ADC_ISENSEF_Pin GPIO_PIN_2
#define ADC_ISENSEF_GPIO_Port GPIOA
#define DTH3_Pin GPIO_PIN_3
#define DTH3_GPIO_Port GPIOA
#define DAC_VCCS_Pin GPIO_PIN_4
#define DAC_VCCS_GPIO_Port GPIOA
#define DAC0_UNUSED_Pin GPIO_PIN_5
#define DAC0_UNUSED_GPIO_Port GPIOA
#define DAC1_UNUSED_Pin GPIO_PIN_6
#define DAC1_UNUSED_GPIO_Port GPIOA
#define ADC0_UNUSED_Pin GPIO_PIN_7
#define ADC0_UNUSED_GPIO_Port GPIOA
#define ADC_VCCSSENSE_Pin GPIO_PIN_4
#define ADC_VCCSSENSE_GPIO_Port GPIOC
#define ADC1_UNUSED_Pin GPIO_PIN_5
#define ADC1_UNUSED_GPIO_Port GPIOC
#define ADC2_UNUSED_Pin GPIO_PIN_0
#define ADC2_UNUSED_GPIO_Port GPIOB
#define ADC_ISENSEC_Pin GPIO_PIN_1
#define ADC_ISENSEC_GPIO_Port GPIOB
#define ADC_DIFF_P_Pin GPIO_PIN_11
#define ADC_DIFF_P_GPIO_Port GPIOF
#define ADC_DIFF_N_Pin GPIO_PIN_12
#define ADC_DIFF_N_GPIO_Port GPIOF
#define ADC_VSENSE_Pin GPIO_PIN_13
#define ADC_VSENSE_GPIO_Port GPIOF
#define DTH2_Pin GPIO_PIN_14
#define DTH2_GPIO_Port GPIOF
#define SD_CARD_DETECT_Pin GPIO_PIN_10
#define SD_CARD_DETECT_GPIO_Port GPIOE
#define SD_CARD_DETECT_EXTI_IRQn EXTI15_10_IRQn
#define SD_CS_Pin GPIO_PIN_13
#define SD_CS_GPIO_Port GPIOE
#define ST_LINK_TX_Pin GPIO_PIN_10
#define ST_LINK_TX_GPIO_Port GPIOB
#define ST_LINK_RX_Pin GPIO_PIN_11
#define ST_LINK_RX_GPIO_Port GPIOB
#define MATC0_Pin GPIO_PIN_12
#define MATC0_GPIO_Port GPIOB
#define MATC1_Pin GPIO_PIN_13
#define MATC1_GPIO_Port GPIOB
#define MATC2_Pin GPIO_PIN_14
#define MATC2_GPIO_Port GPIOB
#define MATC3_Pin GPIO_PIN_15
#define MATC3_GPIO_Port GPIOB
#define FRONT_SW_Pin GPIO_PIN_8
#define FRONT_SW_GPIO_Port GPIOD
#define FRONT_SW_EXTI_IRQn EXTI9_5_IRQn
#define SSR_EN_Pin GPIO_PIN_9
#define SSR_EN_GPIO_Port GPIOD
#define MATR0_Pin GPIO_PIN_10
#define MATR0_GPIO_Port GPIOD
#define MATR1_Pin GPIO_PIN_11
#define MATR1_GPIO_Port GPIOD
#define PWM0_Pin GPIO_PIN_12
#define PWM0_GPIO_Port GPIOD
#define PWM1_Pin GPIO_PIN_13
#define PWM1_GPIO_Port GPIOD
#define MATR2_Pin GPIO_PIN_14
#define MATR2_GPIO_Port GPIOD
#define MATR3_Pin GPIO_PIN_15
#define MATR3_GPIO_Port GPIOD
#define MUX_A_Pin GPIO_PIN_2
#define MUX_A_GPIO_Port GPIOG
#define MUX_B_Pin GPIO_PIN_3
#define MUX_B_GPIO_Port GPIOG
#define ENCODER_A_Pin GPIO_PIN_4
#define ENCODER_A_GPIO_Port GPIOG
#define ENCODER_B_Pin GPIO_PIN_5
#define ENCODER_B_GPIO_Port GPIOG
#define ENCODER_SW_Pin GPIO_PIN_6
#define ENCODER_SW_GPIO_Port GPIOG
#define ENCODER_SW_EXTI_IRQn EXTI9_5_IRQn
#define MUX_C_Pin GPIO_PIN_7
#define MUX_C_GPIO_Port GPIOG
#define DISPL_LED_Pin GPIO_PIN_6
#define DISPL_LED_GPIO_Port GPIOC
#define USB_VBUS_Pin GPIO_PIN_9
#define USB_VBUS_GPIO_Port GPIOA
#define PWM_BUZZER_Pin GPIO_PIN_10
#define PWM_BUZZER_GPIO_Port GPIOA
#define USB_DM_Pin GPIO_PIN_11
#define USB_DM_GPIO_Port GPIOA
#define USB_DP_Pin GPIO_PIN_12
#define USB_DP_GPIO_Port GPIOA
#define ST_LINK_SWDIO_Pin GPIO_PIN_13
#define ST_LINK_SWDIO_GPIO_Port GPIOA
#define ST_LINK_SWCLK_Pin GPIO_PIN_14
#define ST_LINK_SWCLK_GPIO_Port GPIOA
#define TOUCH_CS_Pin GPIO_PIN_10
#define TOUCH_CS_GPIO_Port GPIOC
#define TOUCH_INT_Pin GPIO_PIN_11
#define TOUCH_INT_GPIO_Port GPIOC
#define TOUCH_INT_EXTI_IRQn EXTI15_10_IRQn
#define DISPL_DC_Pin GPIO_PIN_12
#define DISPL_DC_GPIO_Port GPIOC
#define GPIO15_UNUSED_Pin GPIO_PIN_0
#define GPIO15_UNUSED_GPIO_Port GPIOD
#define DISPL_RST_Pin GPIO_PIN_1
#define DISPL_RST_GPIO_Port GPIOD
#define ETH_INT_Pin GPIO_PIN_2
#define ETH_INT_GPIO_Port GPIOD
#define ETH_INT_EXTI_IRQn EXTI2_IRQn
#define ETH_SCK_Pin GPIO_PIN_3
#define ETH_SCK_GPIO_Port GPIOD
#define GPIO14_UNUSED_Pin GPIO_PIN_4
#define GPIO14_UNUSED_GPIO_Port GPIOD
#define GPIO13_UNUSED_Pin GPIO_PIN_5
#define GPIO13_UNUSED_GPIO_Port GPIOD
#define GPIO12_UNUSED_Pin GPIO_PIN_6
#define GPIO12_UNUSED_GPIO_Port GPIOD
#define GPIO11_UNUSED_Pin GPIO_PIN_7
#define GPIO11_UNUSED_GPIO_Port GPIOD
#define GPIO10_UNUSED_Pin GPIO_PIN_10
#define GPIO10_UNUSED_GPIO_Port GPIOG
#define DISPL_SCK_Pin GPIO_PIN_11
#define DISPL_SCK_GPIO_Port GPIOG
#define GPIO9_UNUSED_Pin GPIO_PIN_12
#define GPIO9_UNUSED_GPIO_Port GPIOG
#define GPIO8_UNUSED_Pin GPIO_PIN_13
#define GPIO8_UNUSED_GPIO_Port GPIOG
#define GPIO7_UNUSED_Pin GPIO_PIN_14
#define GPIO7_UNUSED_GPIO_Port GPIOG
#define GPIO6_UNUSED_Pin GPIO_PIN_15
#define GPIO6_UNUSED_GPIO_Port GPIOG
#define ST_LINK_SWO_Pin GPIO_PIN_3
#define ST_LINK_SWO_GPIO_Port GPIOB
#define DISPL_CS_Pin GPIO_PIN_4
#define DISPL_CS_GPIO_Port GPIOB
#define DISPL_MOSI_Pin GPIO_PIN_5
#define DISPL_MOSI_GPIO_Port GPIOB
#define GPIO5_UNUSED_Pin GPIO_PIN_6
#define GPIO5_UNUSED_GPIO_Port GPIOB
#define GPIO4_UNUSED_Pin GPIO_PIN_7
#define GPIO4_UNUSED_GPIO_Port GPIOB
#define GPIO3_UNUSED_Pin GPIO_PIN_8
#define GPIO3_UNUSED_GPIO_Port GPIOB
#define GPIO2_UNUSED_Pin GPIO_PIN_9
#define GPIO2_UNUSED_GPIO_Port GPIOB
#define GPIO1_UNUSED_Pin GPIO_PIN_0
#define GPIO1_UNUSED_GPIO_Port GPIOE
#define GPIO0_UNUSED_Pin GPIO_PIN_1
#define GPIO0_UNUSED_GPIO_Port GPIOE

/* USER CODE BEGIN Private defines */
#define ADC1_DMA_BUF_LEN  8
#define ADC2_DMA_BUF_LEN  3

extern uint16_t adc1_dma_buf[ADC1_DMA_BUF_LEN];
extern uint16_t adc2_dma_buf[ADC2_DMA_BUF_LEN];

/* USER CODE END Private defines */

#ifdef __cplusplus
}
#endif

#endif /* __MAIN_H */

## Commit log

2025-05-07 Useful files
